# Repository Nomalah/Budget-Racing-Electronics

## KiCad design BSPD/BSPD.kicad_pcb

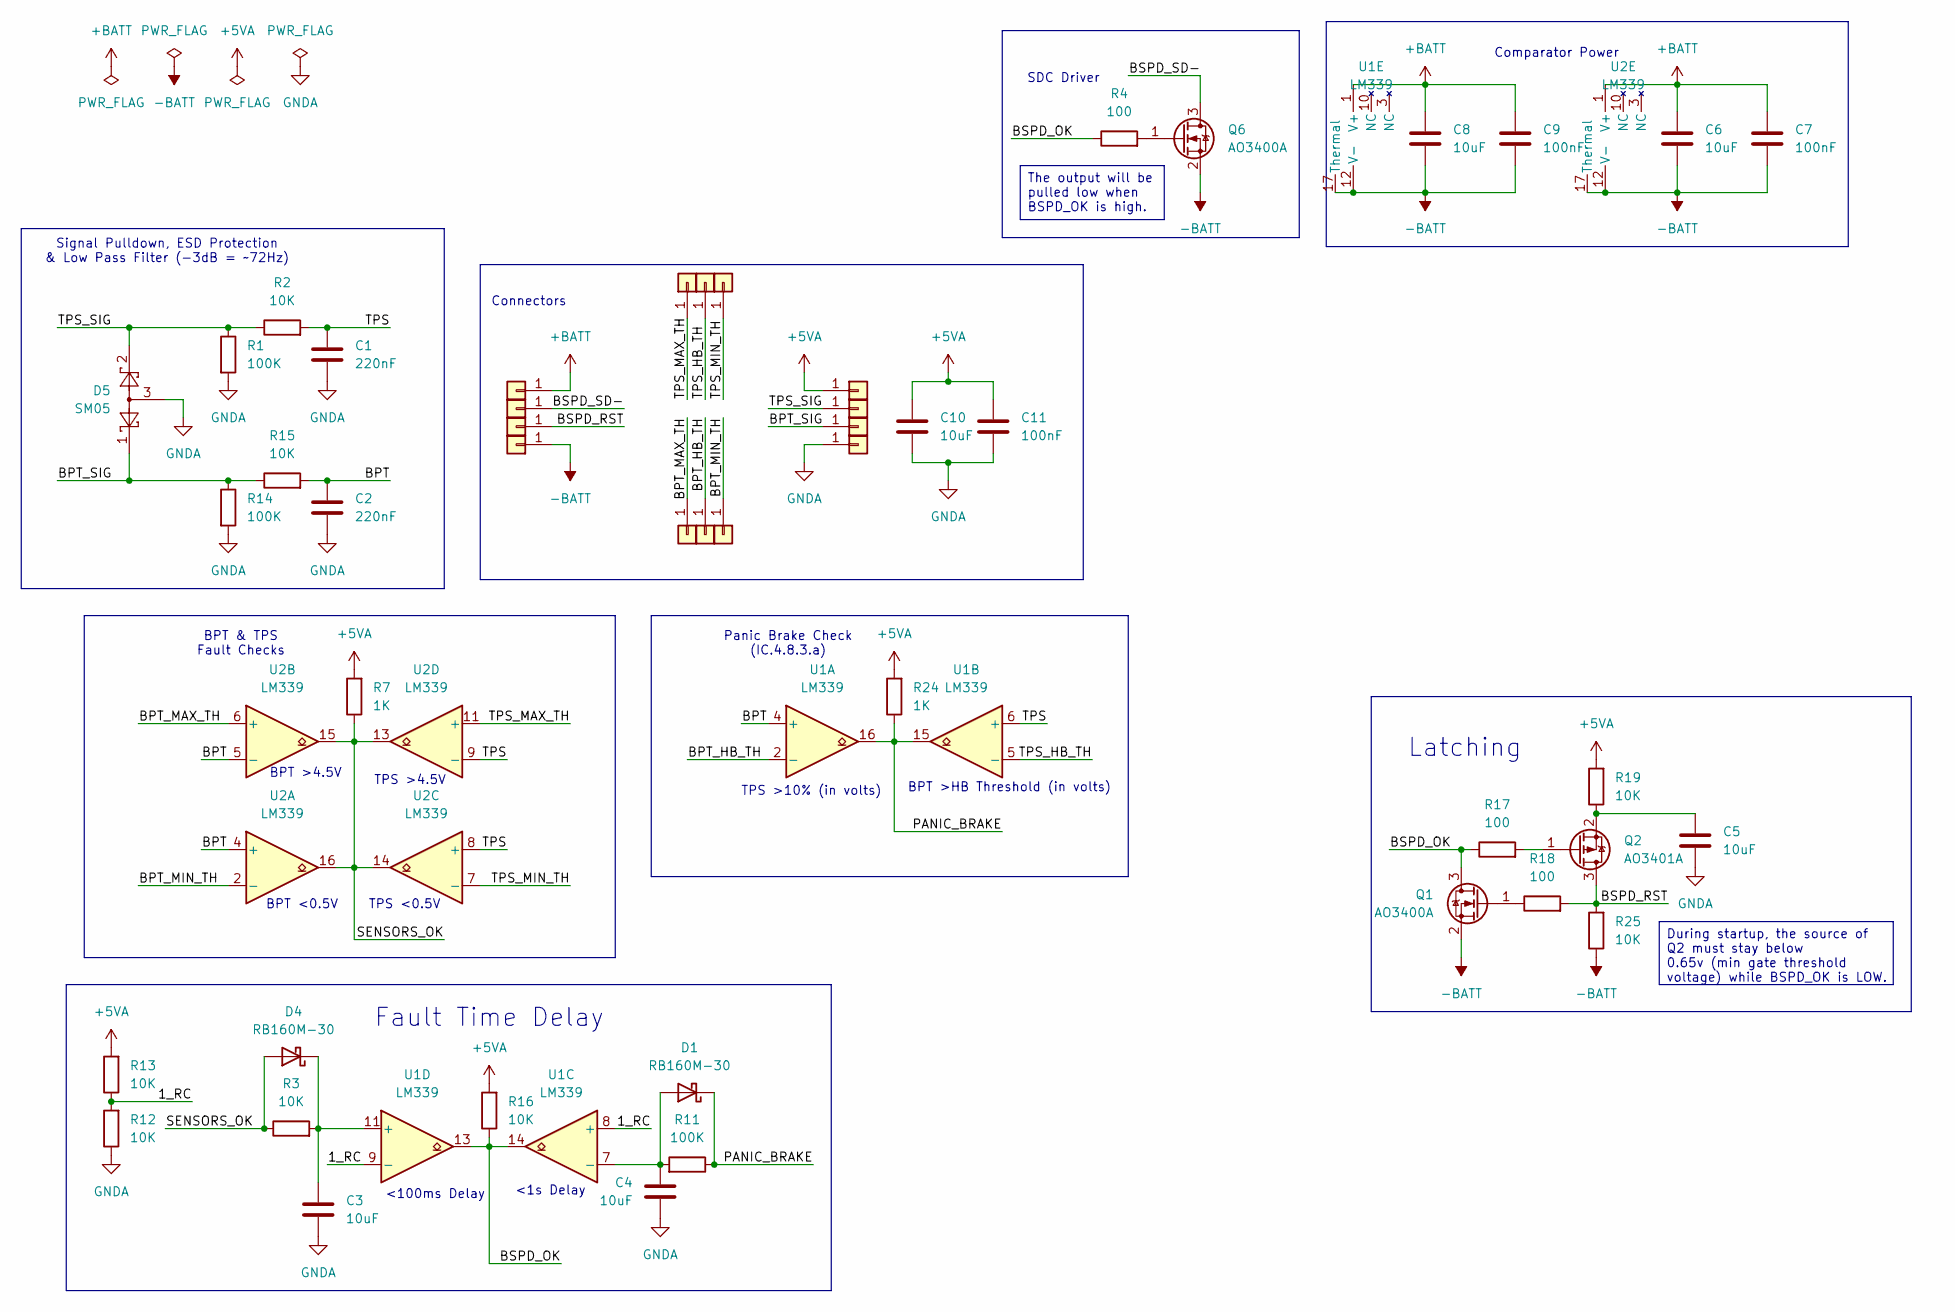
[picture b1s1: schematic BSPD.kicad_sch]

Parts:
C1, C2: 220nF; C_0603_1608Metric
C3, C4, C5, C6, C8, C10: 10uF; C_0603_1608Metric
C7, C9, C11: 100nF; C_0603_1608Metric
D1, D4: RB160M-30; D_SOD-123
D5: SM05; SOT-23
J1: +BATT; PinHeader_1x01_P2.54mm_Vertical
J2, J3, J4, J5, J6, J7, J8, J9, J10, J11, J12, J13, J14: +BATT; PinHeader_1x01_P2.54mm_Circular
Q1, Q6: AO3400A; SOT-23
Q2: AO3401A; SOT-23
R1, R11, R14: 100K; R_0603_1608Metric
R2, R3, R12, R13, R15, R16, R19, R25: 10K; R_0603_1608Metric
R4, R17, R18: 100; R_0603_1608Metric
R7, R24: 1K; R_0603_1608Metric
U1, U2: LM339; WQFN-16-1EP_3x3mm_P0.5mm_EP1.75x1.75mm

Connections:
+5VA: C10.1, C11.1, J11.1, R7.2, R13.2, R16.2, R19.2, R24.2
+BATT: C6.1, C7.1, C8.1, C9.1, J1.1, U1.1 (V+), U2.1 (V+)
-BATT: C6.2, C7.2, C8.2, C9.2, J4.1, Q1.2 (S), Q6.2 (S), R25.1, U1.12 (V-), U1.17 (Thermal), U2.12 (V-), U2.17 (Thermal)
/1_RC: R12.2, R13.1, U1.8 (+), U1.9 (-)
/BPT: C2.1, R15.2, U1.4 (+), U2.4 (+), U2.5 (-)
/BPT_HB_TH: J6.1, U1.2 (-)
/BPT_MAX_TH: J5.1, U2.6 (+)
/BPT_MIN_TH: J7.1, U2.2 (-)
/BPT_SIG: D5.1, J9.1, R14.1, R15.1
/BSPD_OK: Q1.3 (D), R4.1, R16.1, R17.1, U1.13, U1.14
/BSPD_RST: J3.1, Q2.3 (D), R18.2, R25.2
/BSPD_SD-: J2.1, Q6.3 (D)
/PANIC_BRAKE: D1.1 (K), R11.1, R24.1, U1.15, U1.16
/SENSORS_OK: D4.2 (A), R3.1, R7.1, U2.13, U2.14, U2.15, U2.16
/TPS: C1.1, R2.2, U1.6 (+), U2.8 (+), U2.9 (-)
/TPS_HB_TH: J13.1, U1.5 (-)
/TPS_MAX_TH: J14.1, U2.11 (+)
/TPS_MIN_TH: J12.1, U2.7 (-)
/TPS_SIG: D5.2, J10.1, R1.1, R2.1
GNDA: C1.2, C2.2, C3.2, C4.2, C5.2, C10.2, C11.2, D5.3, J8.1, R1.2, R12.1, R14.2
unnamed: C4.1, D1.2 (A), R11.2, U1.7 (-)
unnamed: C3.1, D4.1 (K), R3.2, U1.11 (+)
unnamed: Q1.1 (G), R18.1
unnamed: Q2.1 (G), R17.2
unnamed: C5.1, Q2.2 (S), R19.1
unnamed: Q6.1 (G), R4.2

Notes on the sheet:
Signal Pulldown, ESD Protection & Low Pass Filter (-3dB = ~72Hz)
BPT <0.5V
<100ms Delay
Panic Brake Check (IC.4.8.3.a)
Connectors
BPT >HB Threshold (in volts)
Latching
Fault Time Delay
TPS >10% (in volts)
BPT & TPS Fault Checks
SDC Driver
BPT >4.5V
TPS <0.5V
TPS >4.5V
<1s Delay
Comparator Power
During startup, the source of Q2 must stay below 0.65v (min gate threshold voltage) while BSPD_OK is LOW.
The output will be pulled low when BSPD_OK is high.

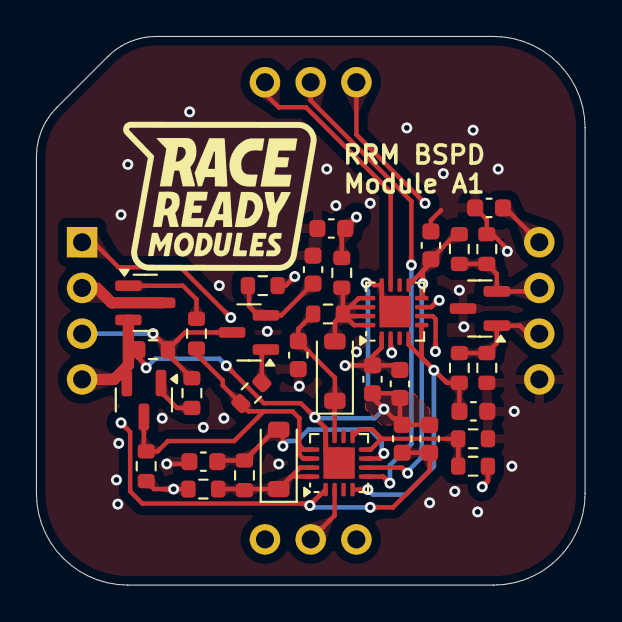
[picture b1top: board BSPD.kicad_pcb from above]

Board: 4 copper layers, 30.5 x 30.5 mm, 49 parts (0 on the bottom side), 26 nets.

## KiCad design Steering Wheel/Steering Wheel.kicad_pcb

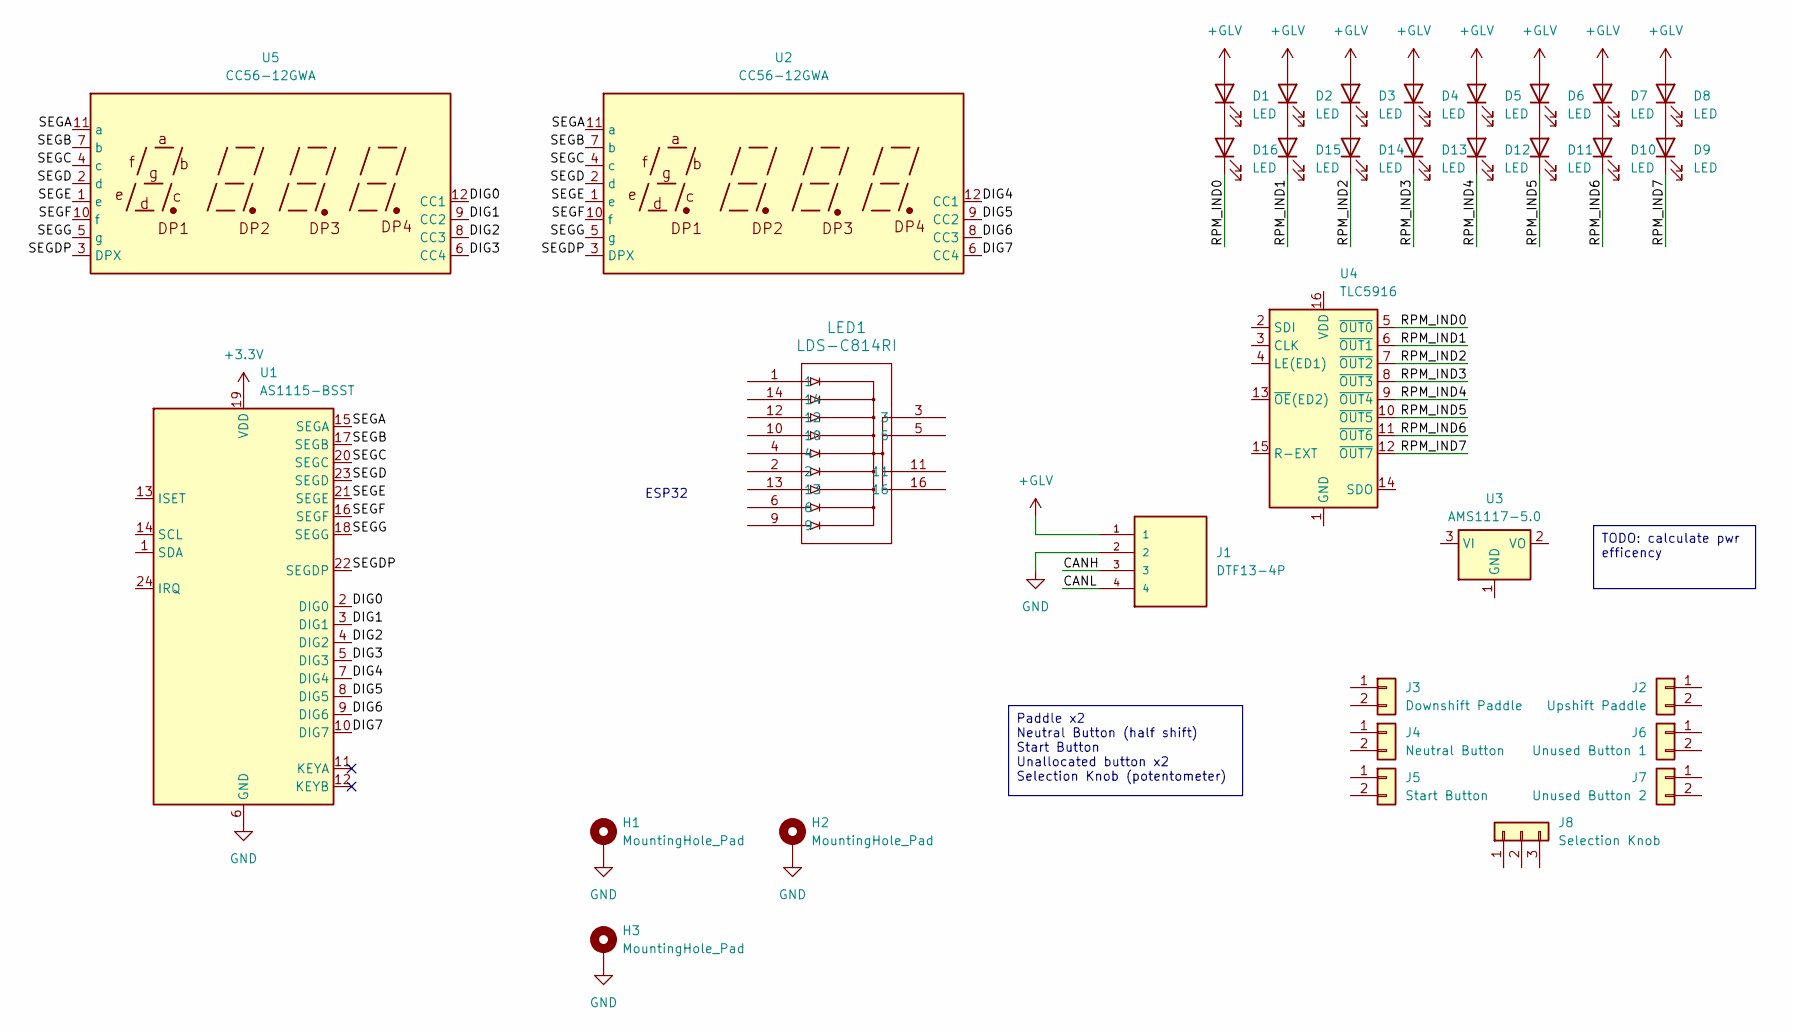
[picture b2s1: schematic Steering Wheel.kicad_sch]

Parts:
D1, D2, D3, D4, D5, D6, D7, D8, D9, D10, D11, D12, D13, D14, D15, D16: LED; LED_1206_3216Metric
H1, H2, H3: MountingHole_Pad; MountingHole_6.5mm_Pad
J1: DTF13-4P; TE_DTF13-4P; MPN DTF13-4P
J2: Upshift Paddle; PinHeader_1x02_P1.00mm_Vertical
J3: Downshift Paddle; PinHeader_1x02_P1.00mm_Vertical
J4: Neutral Button; PinHeader_1x02_P1.00mm_Vertical
J5: Start Button; PinHeader_1x02_P1.00mm_Vertical
J6: Unused Button 1; PinHeader_1x02_P1.00mm_Vertical
J7: Unused Button 2; PinHeader_1x02_P1.00mm_Vertical
J8: Selection Knob; PinHeader_1x03_P1.00mm_Vertical
LED1: LDS-C814RI; LDS-C814RI_LUM
U1: AS1115-BSST; QSOP-24_3.9x8.7mm_P0.635mm
U2, U5: CC56-12GWA
U3: AMS1117-5.0; TO-252-2
U4: TLC5916

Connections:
+3.3V: U1.19 (VDD)
+GLV: D1.2 (A), D2.2 (A), D3.2 (A), D4.2 (A), D5.2 (A), D6.2 (A), D7.2 (A), D8.2 (A), J1.1
/CANH: J1.3
/CANL: J1.4
/DIG0: U1.2 (DIG0), U5.12 (CC1)
/DIG1: U1.3 (DIG1), U5.9 (CC2)
/DIG2: U1.4 (DIG2), U5.8 (CC3)
/DIG3: U1.5 (DIG3), U5.6 (CC4)
/DIG4: U1.7 (DIG4), U2.12 (CC1)
/DIG5: U1.8 (DIG5), U2.9 (CC2)
/DIG6: U1.9 (DIG6), U2.8 (CC3)
/DIG7: U1.10 (DIG7), U2.6 (CC4)
/RPM_IND0: D16.1 (K), U4.5 (~OUT0)
/RPM_IND1: D15.1 (K), U4.6 (~OUT1)
/RPM_IND2: D14.1 (K), U4.7 (~OUT2)
/RPM_IND3: D13.1 (K), U4.8 (~OUT3)
/RPM_IND4: D12.1 (K), U4.9 (~OUT4)
/RPM_IND5: D11.1 (K), U4.10 (~OUT5)
/RPM_IND6: D10.1 (K), U4.11 (~OUT6)
/RPM_IND7: D9.1 (K), U4.12 (~OUT7)
/SEGA: U1.15 (SEGA), U2.11 (a), U5.11 (a)
/SEGB: U1.17 (SEGB), U2.7 (b), U5.7 (b)
/SEGC: U1.20 (SEGC), U2.4 (c), U5.4 (c)
/SEGD: U1.23 (SEGD), U2.2 (d), U5.2 (d)
/SEGDP: U1.22 (SEGDP), U2.3 (DPX), U5.3 (DPX)
/SEGE: U1.21 (SEGE), U2.1 (e), U5.1 (e)
/SEGF: U1.16 (SEGF), U2.10 (f), U5.10 (f)
/SEGG: U1.18 (SEGG), U2.5 (g), U5.5 (g)
GND: H1.1, H2.1, H3.1, J1.2, U1.6 (GND)
unnamed: D1.1 (K), D16.2 (A)
unnamed: D8.1 (K), D9.2 (A)
unnamed: D7.1 (K), D10.2 (A)
unnamed: D6.1 (K), D11.2 (A)
unnamed: D5.1 (K), D12.2 (A)
unnamed: D4.1 (K), D13.2 (A)
unnamed: D3.1 (K), D14.2 (A)
unnamed: D2.1 (K), D15.2 (A)

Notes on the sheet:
Paddle x2 Neutral Button (half shift) Start Button Unallocated button x2 Selection Knob (potentometer)
TODO: calculate pwr efficency
ESP32

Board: 2 copper layers, 32 parts (1 on the bottom side), 26 nets, no tracks yet.

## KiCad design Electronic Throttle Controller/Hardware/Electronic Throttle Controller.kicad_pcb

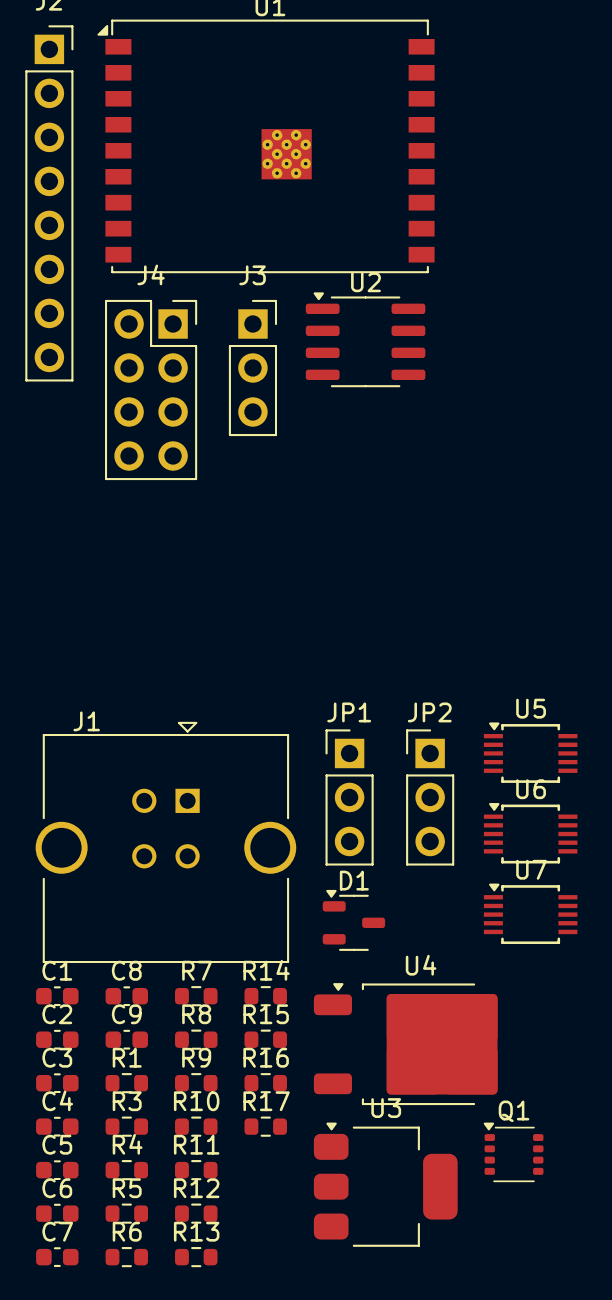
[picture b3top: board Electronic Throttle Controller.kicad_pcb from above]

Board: 2 copper layers, 40 parts (0 on the bottom side), 36 nets, no tracks yet.

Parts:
C1, C2, C3, C4, C5, C6: 150nF; C_0603_1608Metric
C7, C8, C9: 100nF; C_0603_1608Metric
D1: ESD2CAN24-Q1; SOT-23-3
J1: USB_B; USB_B_TE_5787834_Vertical
J2: ETC SIG; PinSocket_1x08_P2.54mm_Vertical
J3: ETC CAN; PinSocket_1x03_P2.54mm_Vertical
J4: ETC PWR; PinSocket_2x04_P2.54mm_Vertical
JP1: Termination Jumper; PinHeader_1x03_P2.54mm_Vertical
JP2: Power Jumper; PinHeader_1x03_P2.54mm_Vertical
Q1: ECH8697R; OnSemi_ECH8
R1: 120; R_0603_1608Metric
R3, R6: 100; R_0603_1608Metric
R4, R5, R15, R16, R17: 10K; R_0603_1608Metric
R7, R8, R9, R10, R11, R12: 12K; R_0603_1608Metric
R13, R14: 4.7K; R_0603_1608Metric
U1: ESP32-C3-WROOM-02U
U2: MCP2551-I-SN; SOIC-8_3.9x4.9mm_P1.27mm
U3: AMS1117-3.3; SOT-223-3_TabPin2
U4: L7805; TO-252-2
U5, U6, U7: ADS1115IDGS; TSSOP-10_3x3mm_P0.5mm

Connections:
+3.3V: R13.1, R14.1, U1.1 (3V3), U2.5 (Vref), U3.2 (VO)
+5V: C7.1, C8.1, C9.1, JP2.2 (C), R15.2, R16.2, R17.2, U2.3 (VDD), U3.3 (VI), U5.8 (VDD), U6.1 (ADDR), U6.8 (VDD), U7.8 (VDD)
+GLV: J4.1, U4.1 (IN)
-BATT: C7.2, C8.2, C9.2, D1.3 (common), J1.4 (GND), J1.5 (Shield), J4.5, J4.6, J4.7, J4.8, Q1.1 (S), Q1.3 (S), R4.1, R5.1, U1.9 (GND), U1.19 (GND), U2.2 (VSS), U3.1 (GND), U4.2 (GND), U5.1 (ADDR), U5.3 (GND), U6.3 (GND), U7.3 (GND)
/APPS1_SIG: J2.2, R7.1
/APPS1_SIGF: C1.2, R7.2, U5.4 (AIN0)
/APPS2_SIG: J2.3, R8.1
/APPS2_SIGF: C2.2, R8.2, U5.6 (AIN2)
/BLIP_SIG: R3.1, R4.2
/BPTF_SIG: J2.4, R9.1
/BPTF_SIGF: C3.2, R9.2, U6.4 (AIN0)
/BPTR_SIG: J2.5, R10.1
/BPTR_SIGF: C4.2, R10.2, U6.6 (AIN2)
/CANH: D1.1 (A1), J3.1, R1.1, U2.7 (CANH)
/CANL: D1.2 (A2), J3.2, JP1.2 (C), U2.6 (CANL)
/CAN_RX: U1.8 (IO9), U2.4 (RXD)
/CAN_TX: U1.7 (IO8), U2.1 (TXD)
/D+: J1.3 (D+), U1.14 (IO19)
/D-: J1.2 (D-), U1.13 (IO18)
/MOTOR_CTRL: R5.2, R6.1, U1.10 (IO10)
/MOTOR_GND: J4.2, J4.3, J4.4, Q1.5 (D), Q1.6 (D), Q1.7 (D), Q1.8 (D)
/SCL: R13.2, U1.5 (IO6), U5.10 (SCL), U6.10 (SCL), U7.1 (ADDR), U7.10 (SCL)
/SDA: R14.2, U1.6 (IO7), U5.9 (SDA), U6.9 (SDA), U7.9 (SDA)
/TPS1_SIG: J2.6, R11.1
/TPS1_SIGF: C5.2, R11.2, U7.4 (AIN0)
/TPS2_SIG: J2.7, R12.1
/TPS2_SIGF: C6.2, R12.2, U7.6 (AIN2)
GNDA: C1.1, C2.1, C3.1, C4.1, C5.1, C6.1, J2.8, U5.5 (AIN1), U5.7 (AIN3), U6.5 (AIN1), U6.7 (AIN3), U7.5 (AIN1), U7.7 (AIN3)
unnamed: JP1.1 (A), R1.2
unnamed: JP2.1 (A), U4.3 (OUT)
unnamed: Q1.2 (G), R3.2
unnamed: Q1.4 (G), R6.2
unnamed: R17.1, U5.2 (ALERT/RDY)
unnamed: R16.1, U6.2 (ALERT/RDY)
unnamed: R15.1, U7.2 (ALERT/RDY)
VBUS: J1.1 (VBUS), JP2.3 (B)

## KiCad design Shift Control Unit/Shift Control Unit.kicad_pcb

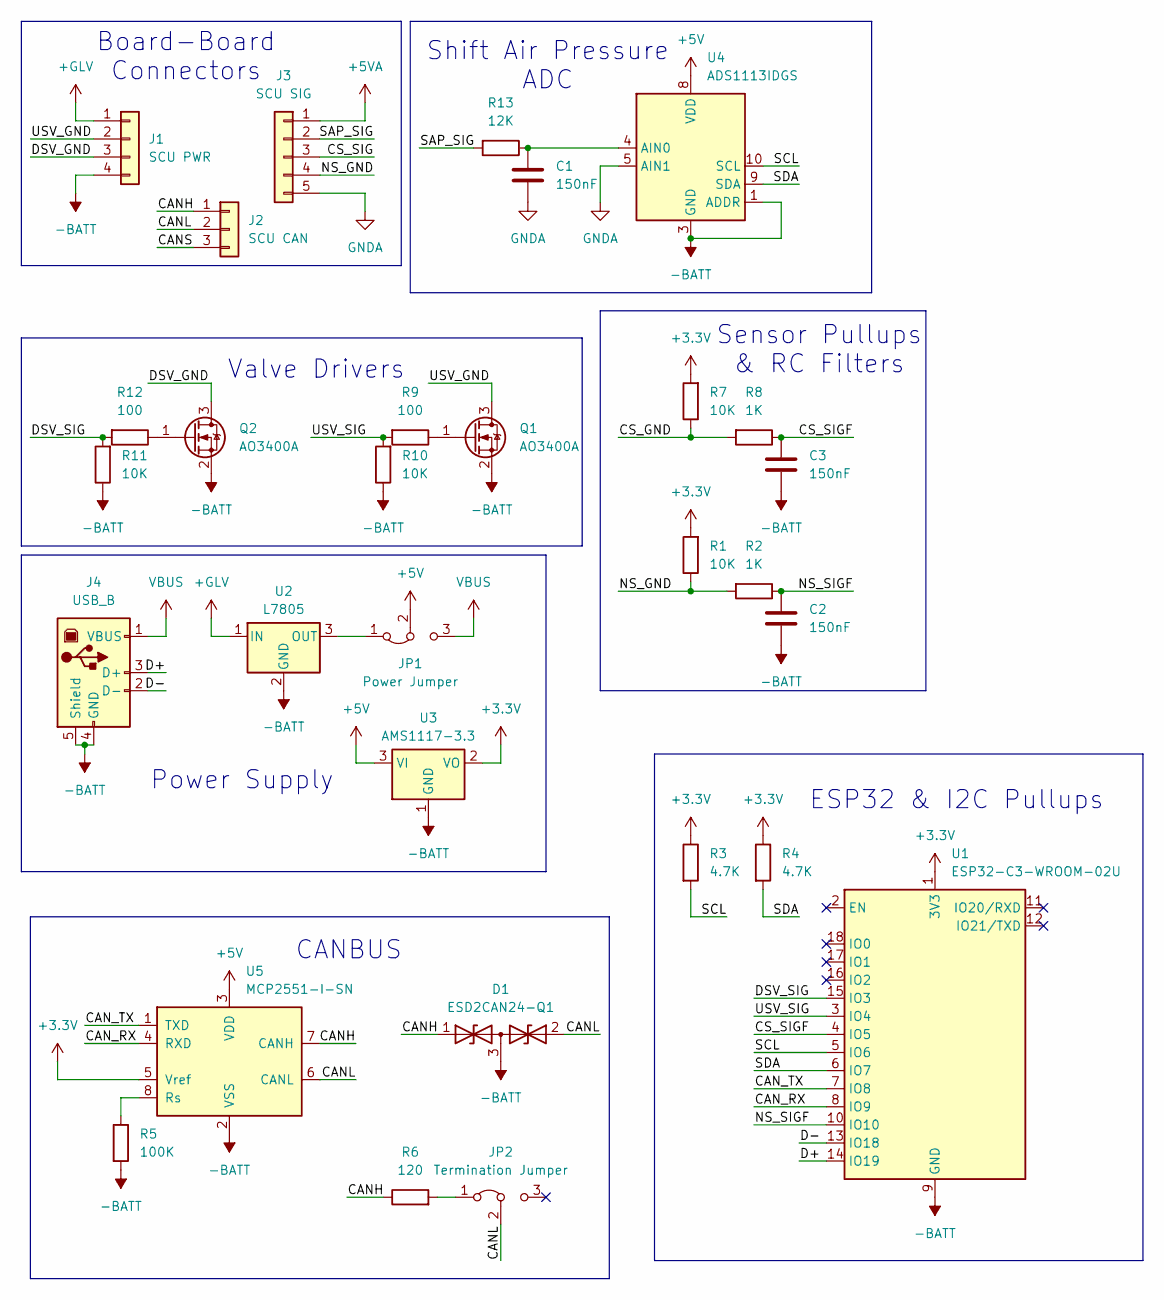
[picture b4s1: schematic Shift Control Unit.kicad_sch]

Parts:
C1, C2, C3: 150nF; C_0603_1608Metric
D1: ESD2CAN24-Q1; SOT-23-3
J1: SCU PWR; PinSocket_1x04_P2.54mm_Vertical
J2: SCU CAN; PinSocket_1x03_P2.54mm_Vertical
J3: SCU SIG; PinSocket_1x05_P2.54mm_Vertical
J4: USB_B; USB_B_TE_5787834_Vertical
JP1: Power Jumper; PinHeader_1x03_P2.54mm_Vertical
JP2: Termination Jumper; PinHeader_1x03_P2.54mm_Vertical
Q1, Q2: AO3400A; SOT-23
R1, R7, R10, R11: 10K; R_0603_1608Metric
R2, R8: 1K; R_0603_1608Metric
R3, R4: 4.7K; R_0603_1608Metric
R5: 100K
R6: 120; R_0603_1608Metric
R9, R12: 100; R_0603_1608Metric
R13: 12K; R_0603_1608Metric
U1: ESP32-C3-WROOM-02U
U2: L7805; TO-252-2
U3: AMS1117-3.3; SOT-223-3_TabPin2
U4: ADS1113IDGS; TSSOP-10_3x3mm_P0.5mm
U5: MCP2551-I-SN; SOIC-8_3.9x4.9mm_P1.27mm

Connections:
+3.3V: R1.2, R3.1, R4.1, R7.2, U1.1 (3V3), U3.2 (VO), U5.5 (Vref)
+5V: JP1.2 (C), U3.3 (VI), U4.8 (VDD), U5.3 (VDD)
+5VA: J3.1
+GLV: J1.1, U2.1 (IN)
-BATT: C2.2, C3.2, D1.3 (common), J1.4, J4.4 (GND), J4.5 (Shield), Q1.2 (S), Q2.2 (S), R5.2, R10.1, R11.1, U1.9 (GND), U1.19 (GND), U2.2 (GND), U3.1 (GND), U4.1 (ADDR), U4.3 (GND), U5.2 (VSS)
/CANH: D1.1 (A1), J2.1, R6.1, U5.7 (CANH)
/CANL: D1.2 (A2), J2.2, JP2.2 (C), U5.6 (CANL)
/CANS: J2.3
/CAN_RX: U1.8 (IO9), U5.4 (RXD)
/CAN_TX: U1.7 (IO8), U5.1 (TXD)
/D+: J4.3 (D+), U1.14 (IO19)
/D-: J4.2 (D-), U1.13 (IO18)
/DSV_GND: J1.3, Q2.3 (D)
/DSV_SIG: R11.2, R12.2, U1.15 (IO3)
/NS_GND: J3.4, R1.1, R2.2
/SAP_SIG: J3.2, R13.2
/SCL: R3.2, U1.5 (IO6), U4.10 (SCL)
/SDA: R4.2, U1.6 (IO7), U4.9 (SDA)
/USV_GND: J1.2, Q1.3 (D)
/USV_SIG: R9.2, R10.2, U1.3 (IO4)
GNDA: C1.2, J3.5, U4.5 (AIN1)
unnamed: JP1.1 (A), U2.3 (OUT)
unnamed: JP2.1 (A), R6.2
unnamed: Q1.1 (G), R9.1
unnamed: Q2.1 (G), R12.1
unnamed: C3.1, R8.1, U1.4 (IO5)
unnamed: C2.1, R2.1, U1.10 (IO10)
unnamed: C1.1, R13.1, U4.4 (AIN0)
unnamed: R5.1, U5.8 (Rs)
VBUS: J4.1 (VBUS), JP1.3 (B)

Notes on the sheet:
Board-Board Connectors
Shift Air Pressure ADC
Sensor Pullups & RC Filters
Power Supply
CANBUS
ESP32 & I2C Pullups
Valve Drivers

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
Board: 2 copper layers, 27 parts (0 on the bottom side), 28 nets, no tracks yet.

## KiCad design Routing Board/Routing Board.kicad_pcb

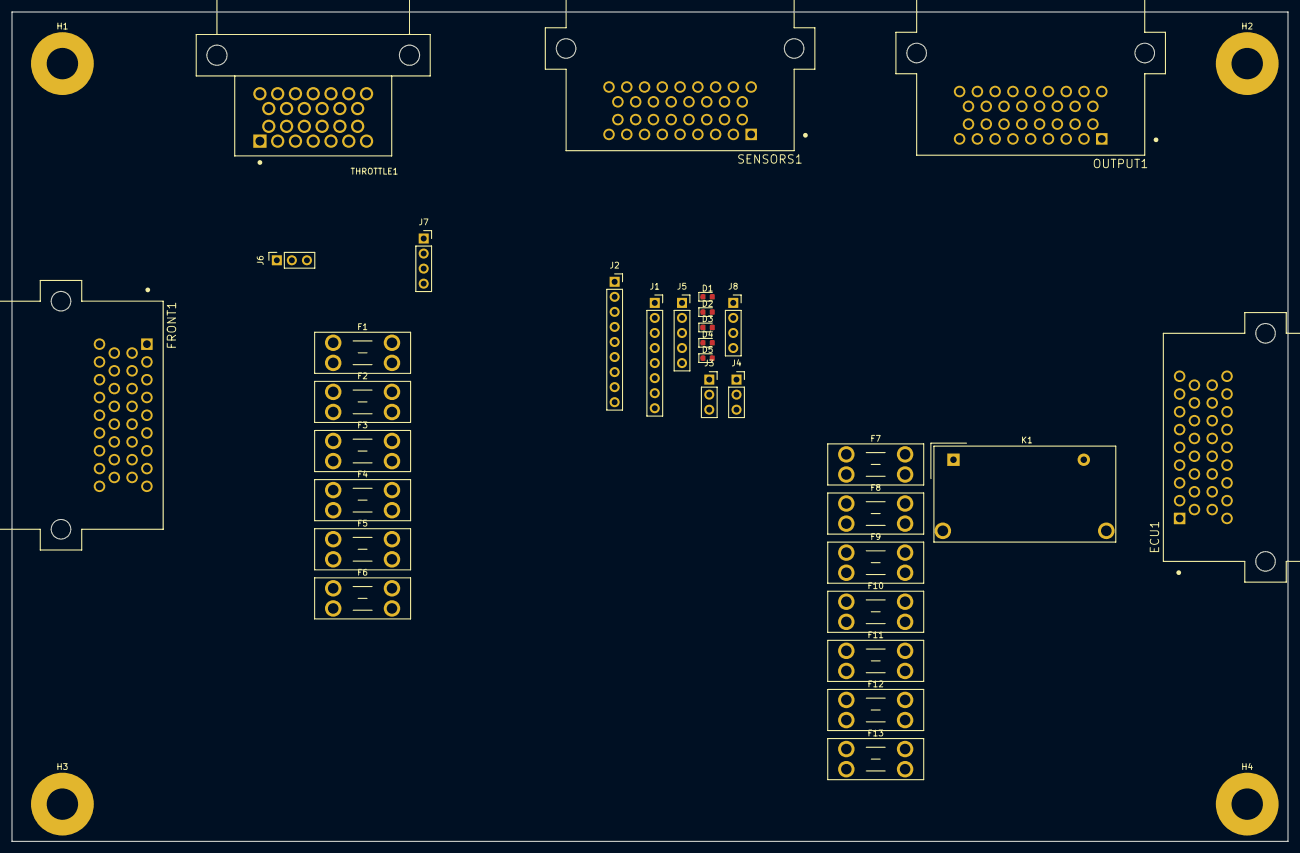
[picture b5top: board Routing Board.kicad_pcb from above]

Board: 2 copper layers, 215.4 x 140.0 mm, 36 parts (0 on the bottom side), 50 nets, no tracks yet.

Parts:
D1, D2, D3, D4, D5: LED; LED_0603_1608Metric
ECU1: 6437288-1; TE_6437288-1
F1: Shift Fuse; Fuseholder_Blade_Mini_Keystone_3568
F2: INJ Fuse; Fuseholder_Blade_Mini_Keystone_3568
F3: IGN Fuse; Fuseholder_Blade_Mini_Keystone_3568
F4: STR Fuse; Fuseholder_Blade_Mini_Keystone_3568
F5: FP Fuse; Fuseholder_Blade_Mini_Keystone_3568
F6: Peripheral Fuse; Fuseholder_Blade_Mini_Keystone_3568
F7: ETB Fuse; Fuseholder_Blade_Mini_Keystone_3568
F8: Sensor Fuse; Fuseholder_Blade_Mini_Keystone_3568
F9: RLM Fuse; Fuseholder_Blade_Mini_Keystone_3568
F10: Wheel Fuse; Fuseholder_Blade_Mini_Keystone_3568
F11: SDC Fuse; Fuseholder_Blade_Mini_Keystone_3568
F12: Lambda Fuse; Fuseholder_Blade_Mini_Keystone_3568
F13: PE3 Fuse; Fuseholder_Blade_Mini_Keystone_3568
FRONT1: 6437288-1; TE_6437288-1
H1, H2, H3, H4: MountingHole_Pad; MountingHole_5.3mm_M5_Pad
J1: ETC SIG; PinSocket_1x08_P2.54mm_Vertical
J2: ETC PWR; PinSocket_1x09_P2.54mm_Vertical
J3: ETC CAN; PinSocket_1x03_P2.54mm_Vertical
J4: SCU CAN; PinSocket_1x03_P2.54mm_Vertical
J5: SCU SIG; PinSocket_1x05_P2.54mm_Vertical
J6: BSPD PWR; PinSocket_1x03_P2.54mm_Vertical
J7: BSPD SIG; PinSocket_1x04_P2.54mm_Vertical
J8: SCU PWR; PinSocket_1x04_P2.54mm_Vertical
K1: SDC Relay; Relay_SPST_Zettler-AZSR131
OUTPUT1: 6437288-2; TE_6437288-2
SENSORS1: 6437288-2; TE_6437288-2
THROTTLE1: 9-6437287-8; TE_9-6437287-8

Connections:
+5VA: F8.2, J1.1, J5.1, J7.1
+GLV: F1.2, F2.1, F6.2, F9.2, F10.1, F12.1, F13.2, FRONT1.4, J2.1, J6.1, J8.1
+SD: F3.1, F4.1, F5.1, F7.1, F11.2
-BATT: D2.1 (K), D3.1 (K), D4.1 (K), D5.1 (K), ECU1.17, ECU1.24, ECU1.25, H1.1, H2.1, H3.1, H4.1, J2.6, J2.7, J2.8, J2.9, J6.3, J8.4
/APPS1_SIG: FRONT1.19, J1.2
/APPS2_SIG: FRONT1.22, J1.3
/BL_12V: F6.1, OUTPUT1.18, OUTPUT1.20, OUTPUT1.22
/BOTS_SD-: FRONT1.5, FRONT1.6
/BPTF_SIG: FRONT1.25, J1.4
/BPTR_SIG: FRONT1.28, J1.5, J7.3
/BSPD_SD-: D1.1 (K), J6.2
/CES_SD+: FRONT1.7, FRONT1.8
/COIL1_GND: ECU1.14, ECU1.16
/CS_SIG: J5.3, SENSORS1.22
/CTS_SIG: ECU1.30, SENSORS1.8
/DSV_12V: F1.1, OUTPUT1.26, OUTPUT1.28
/DSV_GND: J8.3, OUTPUT1.29
/ETC_CANH: ECU1.7, FRONT1.12, J3.1, J4.1, THROTTLE1.3
/ETC_CANL: ECU1.6, FRONT1.13, J3.2, J4.2, THROTTLE1.4
/FPS_SIG: ECU1.4, SENSORS1.6
/FP_12V: F5.2, OUTPUT1.24
/IAT_SIG: ECU1.29, THROTTLE1.19
/IGN1_VCC: F3.2, OUTPUT1.10, OUTPUT1.12, OUTPUT1.14, OUTPUT1.16
/INJ1_GND: ECU1.15, OUTPUT1.2
/INJ1_VCC: F2.2, OUTPUT1.1, OUTPUT1.3, OUTPUT1.5, OUTPUT1.7
/INJ2_GND: ECU1.18, OUTPUT1.4
/INJ3_GND: ECU1.9, OUTPUT1.6
/INJ4_GND: ECU1.12, OUTPUT1.8
/LAMB_12V: F12.2, SENSORS1.26
/LAMB_SIG: ECU1.5, SENSORS1.27
/MAP_SIG: ECU1.19, THROTTLE1.18
/MOTOR_GND: J2.2, J2.3, J2.4, J2.5, THROTTLE1.21
/MOTOR_VCC: F7.2, THROTTLE1.24
/NS_GND: J5.4, SENSORS1.23
/PE3_SENSE_5V: ECU1.23, F8.1
/PE3_VCC: ECU1.34, F13.1
/RLM_12V: F9.1, THROTTLE1.1
/SAP_SIG: J5.2, SENSORS1.19
/STEER_12V: F10.2, FRONT1.10
/STR_VCC: F4.2, OUTPUT1.30
/SYNC_SIG: ECU1.33, SENSORS1.14
/TPS1_SIG: J1.6, J7.2, THROTTLE1.26
/TPS2_SIG: J1.7, THROTTLE1.25
/TRIG_SIG: ECU1.32, SENSORS1.16
/USV_GND: J8.2, OUTPUT1.27
/WSSFL_SIG: ECU1.21, FRONT1.16
/WSSFR_SIG: ECU1.20, FRONT1.2
/WSSRL_SIG: ECU1.11, SENSORS1.30
/WSSRR_SIG: ECU1.3, SENSORS1.33
GNDA: ECU1.8, ECU1.27, FRONT1.14, J1.8, J3.3, J4.3, J5.5, J7.4, THROTTLE1.5

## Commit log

2024-10-17 feat: upload interconnect
2024-11-08 Add BSPD, new components, interconnects, routing board, steering wheel
2024-11-10 feat: began steering wheel schematic
2024-11-24 feat: begin SCU, RLM, PCU, ETC. update SWU
2024-11-24 docs: document bspd rev A errata and update schematic
2024-11-24 feat: begin rev b
    - Change parts to reduce cost (remove extended components)
    - Reset PCB to prep layout
    - Switch to resistor dividers
2024-12-06 Add scope traces
2024-12-06 chore: add scope traces for fault durations
2024-12-07 docs: add documentation for simulation and scope traces
2024-12-13 feat: profile BSPD REV A
2024-12-13 docs: add docs for thresholds @ duty cycle & frequency
2024-12-13 docs: add appendix with profiler schematic
2024-12-13 feat: add onboard regulator to reduce startup requirements
    (not set in stone)
2024-12-19 feat: change to stm32 and add IOC
2026-04-21 BSPD rev 2a
